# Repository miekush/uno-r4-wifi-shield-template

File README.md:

# Arduino UNO R4 WiFi Shield Template

This is a super simple template for creating custom shields for the Arduino UNO R4 WiFi in KiCad V7

# Installation

1. Clone repo to a folder of your choice
2. Open the project in KiCad V7
3. "Save As" with the name of your project
4. Enjoy! :)

# License

MKE supports the open source hardware community by sharing hardware design files freely on GitHub!

Designed by Mike Kushnerik (miekush)

Licensed under [Creative Commons Attribution-ShareAlike CC BY-SA 4.0](http://creativecommons.org/licenses/by-sa/4.0/)

All text above must be included in any redistribution!

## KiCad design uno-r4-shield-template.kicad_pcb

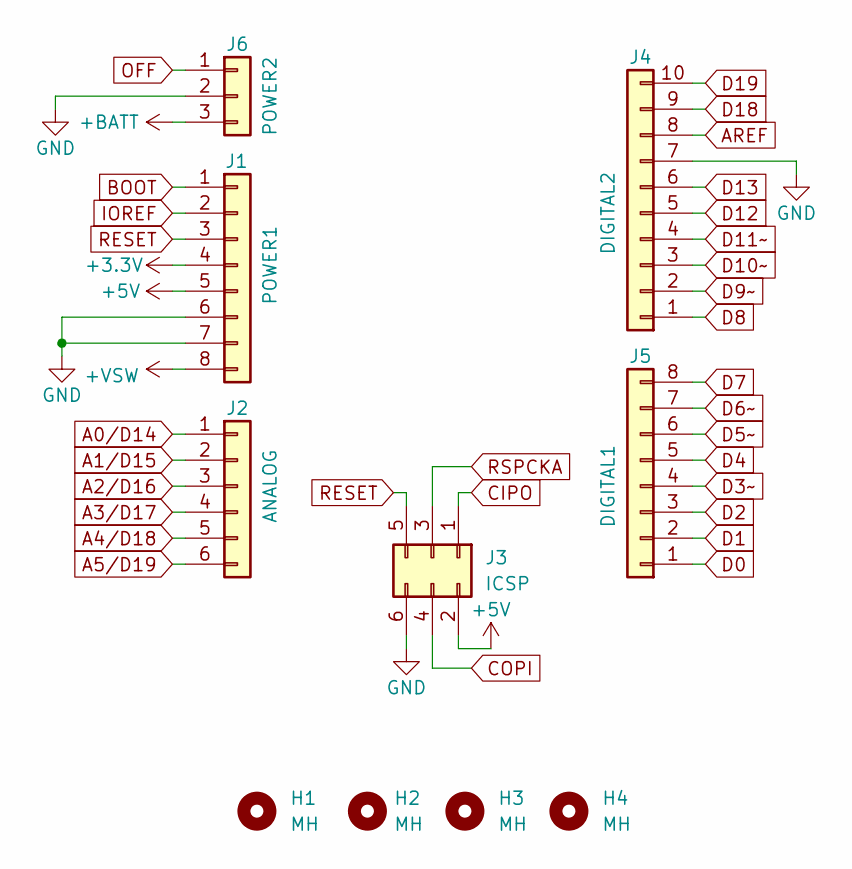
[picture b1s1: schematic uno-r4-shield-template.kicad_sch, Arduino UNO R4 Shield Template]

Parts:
H1, H2, H3, H4: MH; MountingHole_3.2mm_M3
J1: POWER1; PinHeader_1x08_P2.54mm_Vertical
J2: ANALOG; PinHeader_1x06_P2.54mm_Vertical
J3: ICSP; PinSocket_2x03_P2.54mm_Vertical
J4: DIGITAL2; PinHeader_1x10_P2.54mm_Vertical
J5: DIGITAL1; PinHeader_1x08_P2.54mm_Vertical
J6: POWER2; PinSocket_1x03_P2.54mm_Vertical

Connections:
+3V3: J1.4
+5V: J1.5, J3.2
+BATT: J6.3
+VSW: J1.8
A0/D14: J2.1
A1/D15: J2.2
A2/D16: J2.3
A3/D17: J2.4
A4/D18: J2.5
A5/D19: J2.6
AREF: J4.8
BOOT: J1.1
CIPO: J3.1
COPI: J3.4
D0: J5.1
D1: J5.2
D2: J5.3
D3~: J5.4
D4: J5.5
D5~: J5.6
D6~: J5.7
D7: J5.8
D8: J4.1
D9~: J4.2
D10~: J4.3
D11~: J4.4
D12: J4.5
D13: J4.6
D18: J4.9
D19: J4.10
GND: J1.6, J1.7, J3.6, J4.7, J6.2
IOREF: J1.2
OFF: J6.1
RESET: J1.3, J3.5
RSPCKA: J3.3

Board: 2 copper layers, 50 parts (6 on the bottom side), 3 nets, no tracks yet.

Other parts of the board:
kibuzzard-64EA1AE1: G***; kibuzzard-64EA1AE1
kibuzzard-64EA1B1D: G***; kibuzzard-64EA1B1D
kibuzzard-64EA1B42: G***; kibuzzard-64EA1B42
kibuzzard-64EA15CB: G***; kibuzzard-64EA15CB
kibuzzard-64EA16B9: G***; kibuzzard-64EA16B9
kibuzzard-64EA17CF: G***; kibuzzard-64EA17CF
kibuzzard-64EA153F: G***; kibuzzard-64EA153F
kibuzzard-64EA162C: G***; kibuzzard-64EA162C
kibuzzard-64EA177C: G***; kibuzzard-64EA177C
kibuzzard-64EA1511: G***; kibuzzard-64EA1511
kibuzzard-64EA1739: G***; kibuzzard-64EA1739
kibuzzard-64EA1767: G***; kibuzzard-64EA1767
kibuzzard-64EA1802: G***; kibuzzard-64EA1802
kibuzzard-64EA1958: G***; kibuzzard-64EA1958
kibuzzard-636462BB: G***; kibuzzard-636462BB
kibuzzard-636463B1: G***; kibuzzard-636463B1
kibuzzard-636463C7: G***; kibuzzard-636463C7
kibuzzard-636463E3: G***; kibuzzard-636463E3
kibuzzard-636464C1: G***; kibuzzard-636464C1
kibuzzard-636464E7: G***; kibuzzard-636464E7
kibuzzard-636465A9: G***; kibuzzard-636465A9
kibuzzard-636466AF: G***; kibuzzard-636466AF
kibuzzard-6364607A: G***; kibuzzard-6364607A
kibuzzard-6364651D: G***; kibuzzard-6364651D
kibuzzard-6364657A: G***; kibuzzard-6364657A
kibuzzard-6364668F: G***; kibuzzard-6364668F
kibuzzard-6364669B: G***; kibuzzard-6364669B
kibuzzard-6365405C: G***; kibuzzard-6365405C
kibuzzard-63646068: G***; kibuzzard-63646068
kibuzzard-63646358: G***; kibuzzard-63646358
kibuzzard-63646507: G***; kibuzzard-63646507
kibuzzard-63646512: G***; kibuzzard-63646512
kibuzzard-63646593: G***; kibuzzard-63646593
kibuzzard-63646605: G***; kibuzzard-63646605
kibuzzard-63646671: G***; kibuzzard-63646671
kibuzzard-63646688: G***; kibuzzard-63646688
kibuzzard-63646694: G***; kibuzzard-63646694
kibuzzard-63656678: G***; kibuzzard-63656678
kibuzzard-63659483: G***; kibuzzard-63659483
kibuzzard-63659489: G***; kibuzzard-63659489

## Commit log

2023-08-26 Initial upload
2023-08-26 Update image
